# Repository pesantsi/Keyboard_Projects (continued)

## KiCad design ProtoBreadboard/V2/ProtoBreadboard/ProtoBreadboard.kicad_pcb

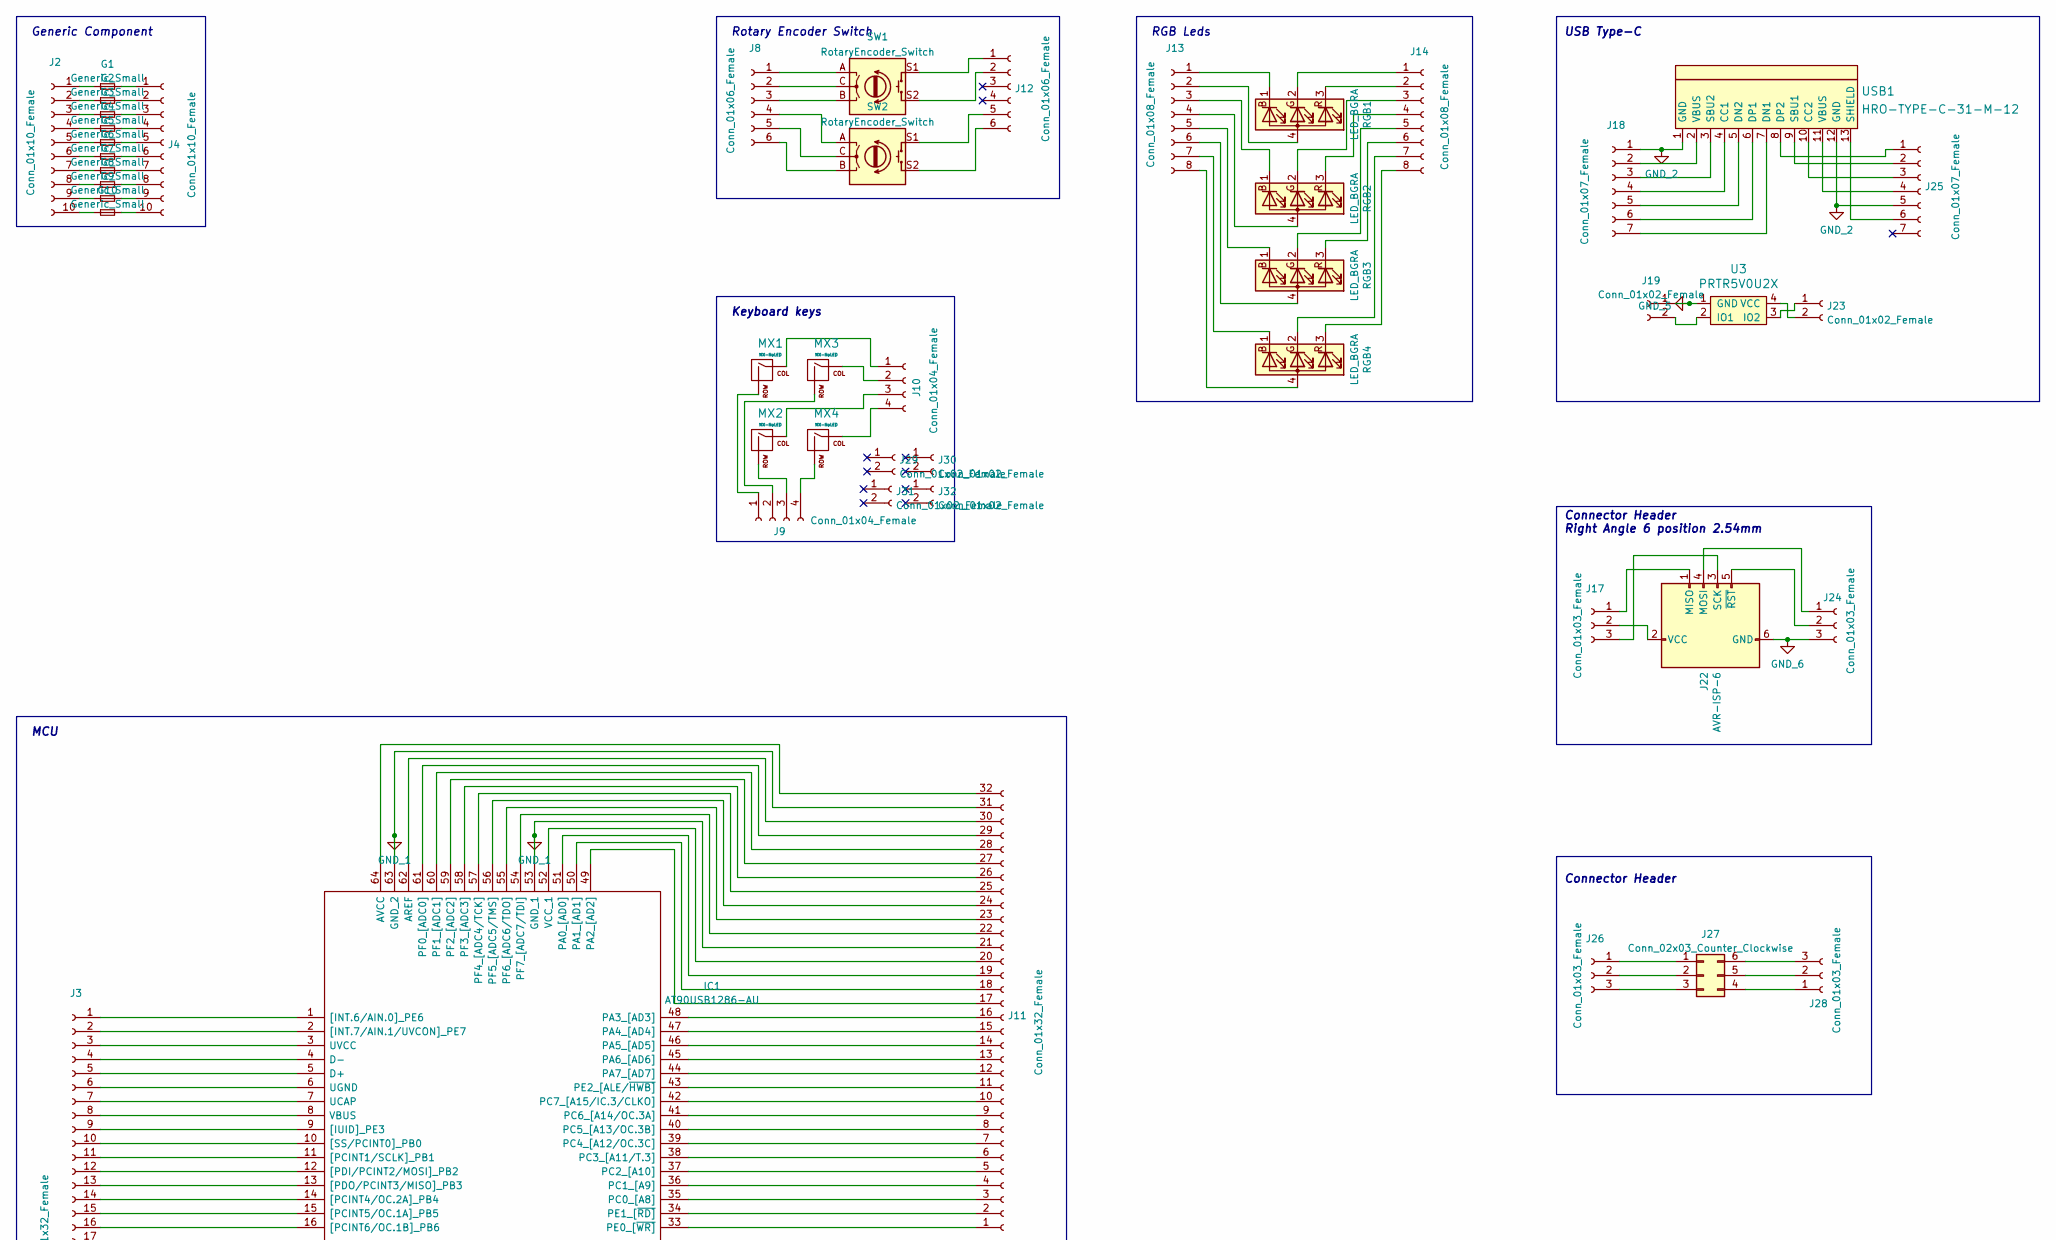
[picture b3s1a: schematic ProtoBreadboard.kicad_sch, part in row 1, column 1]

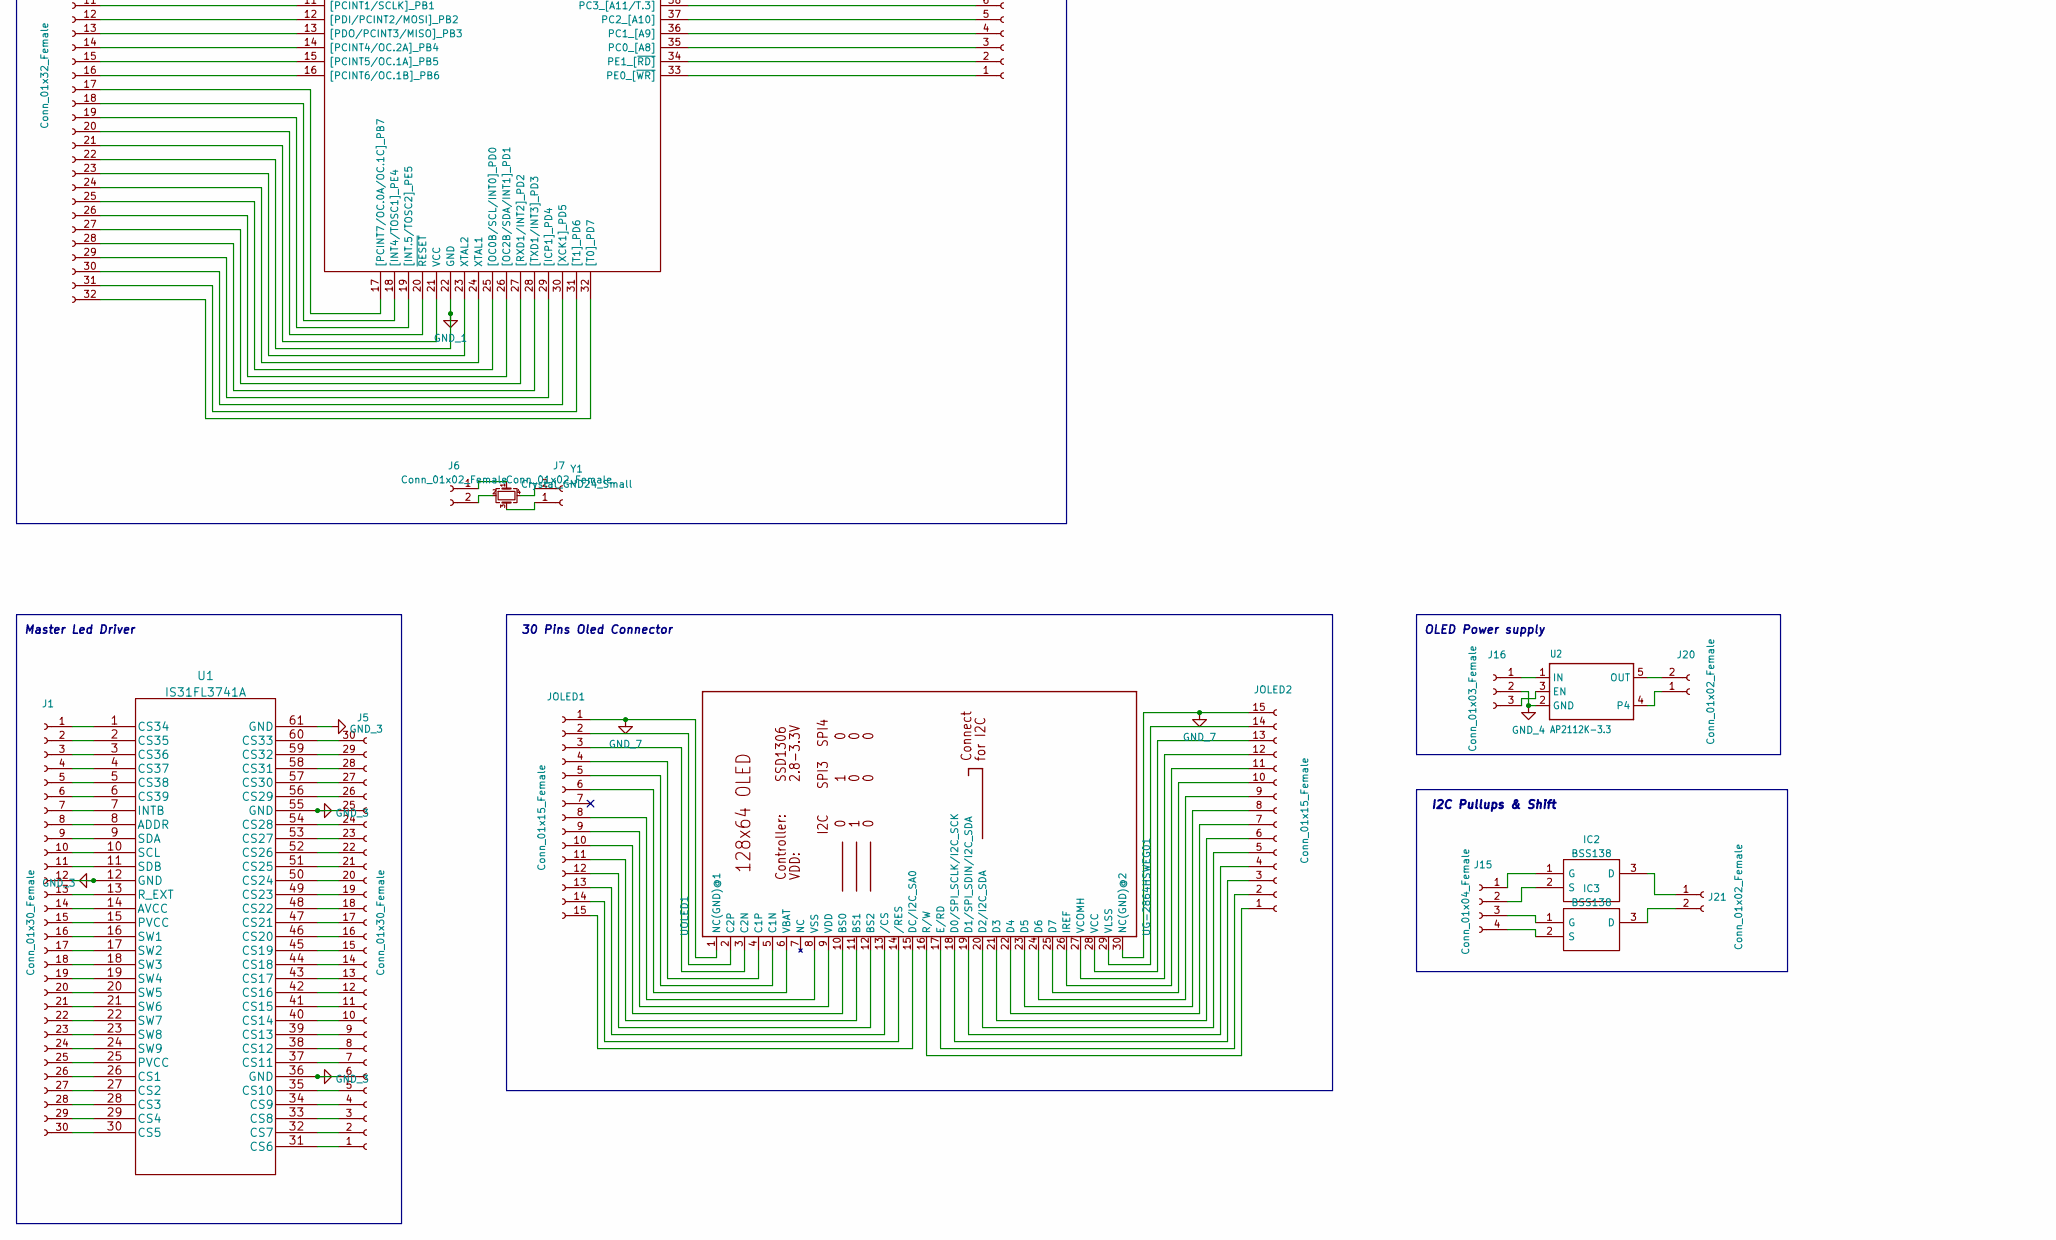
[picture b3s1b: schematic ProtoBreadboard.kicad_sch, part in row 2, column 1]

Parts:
G1, G2, G3, G4, G5, G6, G7, G8, G9, G10: Generic_Small; Generic
IC1: AT90USB1286-AU; Mouser Part Number 556-AT90USB1286-AU
IC2, IC3: BSS138; SOT95P240X120-3N; Manufacturer_Part_Number BSS138; Mouser Part Number 512-BSS138
J1, J5: Conn_01x30_Female; PinHeader_1x30_P2.54mm_Vertical
J2, J4: Conn_01x10_Female; PinHeader_1x10_P2.54mm_Vertical
J3, J11: Conn_01x32_Female; PinHeader_1x32_P2.54mm_Vertical
J6, J7, J19, J20, J21, J23, J29, J30, J31, J32: Conn_01x02_Female; PinHeader_1x02_P2.54mm_Vertical
J8, J12: Conn_01x06_Female; PinHeader_1x06_P2.54mm_Vertical
J9, J10, J15: Conn_01x04_Female; PinHeader_1x04_P2.54mm_Vertical
J13, J14: Conn_01x08_Female; PinHeader_1x08_P2.54mm_Vertical
J16, J17, J24, J26, J28: Conn_01x03_Female; PinHeader_1x03_P2.54mm_Vertical
J18, J25: Conn_01x07_Female; PinHeader_1x07_P2.54mm_Vertical
J22: AVR-ISP-6; PinHeader_2x03_P2.54mm_Vertical
J27: Conn_02x03_Counter_Clockwise; PinHeader_2x03_P2.54mm_Vertical
JOLED1, JOLED2: Conn_01x15_Female; PinHeader_1x15_P2.54mm_Vertical
MX1, MX2, MX3, MX4: MX-NoLED; MXOnly-1U-NoLED_3Pins
RGB1, RGB2, RGB3, RGB4: LED_BGRA; QBLP677R-RGB
SW1, SW2: RotaryEncoder_Switch; RotaryEncoder_Alps_EC12E-Switch_Vertical_H20mm
U1: IS31FL3741A; QFN40P700X700X80-61N-D
U2: AP2112K-3.3; SOT-23-5
U3: PRTR5V0U2X; SOT143B
UOLED1: UG-2864HSWEG01; 5051103091
USB1: HRO-TYPE-C-31-M-12
Y1: Crystal_GND24_Small; Crystal_SMD_3225-4Pin_3.2x2.5mm

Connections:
GND_1: IC1.22 (GND), IC1.53 (GND_1), IC1.63 (GND_2), J3.22, J11.21, J11.31
GND_2: J18.1, J25.5, USB1.1 (GND), USB1.12 (GND)
GND_3: J1.12, J5.6, J5.25, U1.12 (GND), U1.36 (GND), U1.55 (GND), U1.61 (GND)
GND_4: J16.2, U2.2 (GND)
GND_5: J19.1, U3.1 (GND)
GND_6: J22.6 (GND), J24.3
GND_7: JOLED1.1, JOLED2.15, UOLED1.1 (NC(GND)@1), UOLED1.30 (NC(GND)@2)
unnamed: G1.1, J2.1
unnamed: G1.2, J4.1
unnamed: G2.1, J2.2
unnamed: G2.2, J4.2
unnamed: G3.1, J2.3
unnamed: G3.2, J4.3
unnamed: G4.1, J2.4
unnamed: G4.2, J4.4
unnamed: G5.1, J2.5
unnamed: G5.2, J4.5
unnamed: G6.1, J2.6
unnamed: G6.2, J4.6
unnamed: G7.1, J2.7
unnamed: G7.2, J4.7
unnamed: G8.1, J2.8
unnamed: G8.2, J4.8
unnamed: G9.1, J2.9
unnamed: G9.2, J4.9
unnamed: G10.1, J2.10
unnamed: G10.2, J4.10
unnamed: IC1.1 ([INT.6/AIN.0]_PE6), J3.1
unnamed: IC1.2 ([INT.7/AIN.1/UVCON]_PE7), J3.2
unnamed: IC1.3 (UVCC), J3.3
unnamed: IC1.4 (D-), J3.4
unnamed: IC1.5 (D+), J3.5
unnamed: IC1.6 (UGND), J3.6
unnamed: IC1.7 (UCAP), J3.7
unnamed: IC1.8 (VBUS), J3.8
unnamed: IC1.9 ([IUID]_PE3), J3.9
unnamed: IC1.10 ([SS/PCINT0]_PB0), J3.10
unnamed: IC1.11 ([PCINT1/SCLK]_PB1), J3.11
unnamed: IC1.12 ([PDI/PCINT2/MOSI]_PB2), J3.12
unnamed: IC1.13 ([PDO/PCINT3/MISO]_PB3), J3.13
unnamed: IC1.14 ([PCINT4/OC.2A]_PB4), J3.14
unnamed: IC1.15 ([PCINT5/OC.1A]_PB5), J3.15
unnamed: IC1.16 ([PCINT6/OC.1B]_PB6), J3.16
unnamed: IC1.17 ([PCINT7/OC.0A/OC.1C]_PB7), J3.17
unnamed: IC1.18 ([INT4/TOSC1]_PE4), J3.18
unnamed: IC1.19 ([INT.5/TOSC2]_PE5), J3.19
unnamed: IC1.20 (~RESET), J3.20
unnamed: IC1.21 (VCC), J3.21
unnamed: IC1.23 (XTAL2), J3.23
unnamed: IC1.24 (XTAL1), J3.24
unnamed: IC1.25 ([OC0B/SCL/INT0]_PD0), J3.25
unnamed: IC1.26 ([OC2B/SDA/INT1]_PD1), J3.26
unnamed: IC1.27 ([RXD1/INT2]_PD2), J3.27
unnamed: IC1.28 ([TXD1/INT3]_PD3), J3.28
unnamed: IC1.29 ([ICP1]_PD4), J3.29
unnamed: IC1.30 ([XCK1]_PD5), J3.30
unnamed: IC1.31 ([T1]_PD6), J3.31
unnamed: IC1.32 ([T0]_PD7), J3.32
unnamed: IC1.33 (PE0_[~WR]), J11.1
unnamed: IC1.34 (PE1_[~RD]), J11.2
unnamed: IC1.35 (PC0_[A8]), J11.3
unnamed: IC1.36 (PC1_[A9]), J11.4
unnamed: IC1.37 (PC2_[A10]), J11.5
unnamed: IC1.38 (PC3_[A11/T.3]), J11.6
unnamed: IC1.39 (PC4_[A12/OC.3C]), J11.7
unnamed: IC1.40 (PC5_[A13/OC.3B]), J11.8
unnamed: IC1.41 (PC6_[A14/OC.3A]), J11.9
unnamed: IC1.42 (PC7_[A15/IC.3/CLKO]), J11.10
unnamed: IC1.43 (PE2_[ALE/~HWB]), J11.11
unnamed: IC1.44 (PA7_[AD7]), J11.12
unnamed: IC1.45 (PA6_[AD6]), J11.13
unnamed: IC1.46 (PA5_[AD5]), J11.14
unnamed: IC1.47 (PA4_[AD4]), J11.15
unnamed: IC1.48 (PA3_[AD3]), J11.16
unnamed: IC1.49 (PA2_[AD2]), J11.17
unnamed: IC1.50 (PA1_[AD1]), J11.18
unnamed: IC1.51 (PA0_[AD0]), J11.19
unnamed: IC1.52 (VCC_1), J11.20
unnamed: IC1.54 (PF7_[ADC7/TDI]), J11.22
unnamed: IC1.55 (PF6_[ADC6/TDO]), J11.23
unnamed: IC1.56 (PF5_[ADC5/TMS]), J11.24
unnamed: IC1.57 (PF4_[ADC4/TCK]), J11.25
unnamed: IC1.58 (PF3_[ADC3]), J11.26
unnamed: IC1.59 (PF2_[ADC2]), J11.27
unnamed: IC1.60 (PF1_[ADC1]), J11.28
unnamed: IC1.61 (PF0_[ADC0]), J11.29
unnamed: IC1.62 (AREF), J11.30
unnamed: IC1.64 (AVCC), J11.32
unnamed: IC2.1 (G), J15.1
unnamed: IC2.2 (S), J15.2
unnamed: IC2.3 (D), J21.1
unnamed: IC3.1 (G), J15.3
unnamed: IC3.2 (S), J15.4
unnamed: IC3.3 (D), J21.2
unnamed: J1.1, U1.1 (CS34)
unnamed: J1.2, U1.2 (CS35)
unnamed: J1.3, U1.3 (CS36)
unnamed: J1.4, U1.4 (CS37)
unnamed: J1.5, U1.5 (CS38)
unnamed: J1.6, U1.6 (CS39)
unnamed: J1.7, U1.7 (INTB)
unnamed: J1.8, U1.8 (ADDR)
unnamed: J1.9, U1.9 (SDA)
unnamed: J1.10, U1.10 (SCL)
unnamed: J1.11, U1.11 (SDB)
unnamed: J1.13, U1.13 (R_EXT)
unnamed: J1.14, U1.14 (AVCC)
unnamed: J1.15, U1.15 (PVCC)
unnamed: J1.16, U1.16 (SW1)
unnamed: J1.17, U1.17 (SW2)
unnamed: J1.18, U1.18 (SW3)
unnamed: J1.19, U1.19 (SW4)
unnamed: J1.20, U1.20 (SW5)
unnamed: J1.21, U1.21 (SW6)
unnamed: J1.22, U1.22 (SW7)
unnamed: J1.23, U1.23 (SW8)
unnamed: J1.24, U1.24 (SW9)
unnamed: J1.25, U1.25 (PVCC)
unnamed: J1.26, U1.26 (CS1)
unnamed: J1.27, U1.27 (CS2)
unnamed: J1.28, U1.28 (CS3)
unnamed: J1.29, U1.29 (CS4)
unnamed: J1.30, U1.30 (CS5)
unnamed: J5.1, U1.31 (CS6)
unnamed: J5.2, U1.32 (CS7)
unnamed: J5.3, U1.33 (CS8)
unnamed: J5.4, U1.34 (CS9)
unnamed: J5.5, U1.35 (CS10)
unnamed: J5.7, U1.37 (CS11)
unnamed: J5.8, U1.38 (CS12)
unnamed: J5.9, U1.39 (CS13)
unnamed: J5.10, U1.40 (CS14)
unnamed: J5.11, U1.41 (CS15)
unnamed: J5.12, U1.42 (CS16)
unnamed: J5.13, U1.43 (CS17)
unnamed: J5.14, U1.44 (CS18)
unnamed: J5.15, U1.45 (CS19)
unnamed: J5.16, U1.46 (CS20)
unnamed: J5.17, U1.47 (CS21)
unnamed: J5.18, U1.48 (CS22)
unnamed: J5.19, U1.49 (CS23)
unnamed: J5.20, U1.50 (CS24)
unnamed: J5.21, U1.51 (CS25)
unnamed: J5.22, U1.52 (CS26)
unnamed: J5.23, U1.53 (CS27)
unnamed: J5.24, U1.54 (CS28)
unnamed: J5.26, U1.56 (CS29)
unnamed: J5.27, U1.57 (CS30)
unnamed: J5.28, U1.58 (CS31)
unnamed: J5.29, U1.59 (CS32)
unnamed: J5.30, U1.60 (CS33)
unnamed: J6.1, Y1.1
unnamed: J6.2, Y1.2
unnamed: J7.1, Y1.3
unnamed: J7.2, Y1.4
unnamed: J8.1, SW1.A
unnamed: J8.2, SW1.C
unnamed: J8.3, SW1.B
unnamed: J8.4, SW2.A
unnamed: J8.5, SW2.C
unnamed: J8.6, SW2.B
unnamed: J9.1, MX1.2 (ROW)
unnamed: J9.2, MX3.2 (ROW)
unnamed: J9.3, MX2.2 (ROW)
unnamed: J9.4, MX4.2 (ROW)
unnamed: J10.1, MX1.1 (COL)
unnamed: J10.2, MX3.1 (COL)
unnamed: J10.3, MX2.1 (COL)
unnamed: J10.4, MX4.1 (COL)
unnamed: J13.1, RGB1.1 (BK)
unnamed: J13.2, RGB1.4 (A)
unnamed: J13.3, RGB2.1 (BK)
unnamed: J13.4, RGB2.4 (A)
unnamed: J13.5, RGB3.1 (BK)
unnamed: J13.6, RGB3.4 (A)
unnamed: J13.7, RGB4.1 (BK)
unnamed: J13.8, RGB4.4 (A)
unnamed: J14.1, RGB1.2 (GK)
unnamed: J14.2, RGB1.3 (RK)
unnamed: J14.3, RGB2.2 (GK)
unnamed: J14.4, RGB2.3 (RK)
unnamed: J14.5, RGB3.2 (GK)
unnamed: J14.6, RGB3.3 (RK)
unnamed: J14.7, RGB4.2 (GK)
unnamed: J14.8, RGB4.3 (RK)
unnamed: J16.1, U2.1 (IN)
unnamed: J16.3, U2.3 (EN)
unnamed: J17.1, J22.1 (MISO)
unnamed: J17.2, J22.2 (VCC)
unnamed: J17.3, J22.3 (SCK)
unnamed: J18.2, USB1.2 (VBUS)
unnamed: J18.3, USB1.3 (SBU2)
unnamed: J18.4, USB1.4 (CC1)
unnamed: J18.5, USB1.5 (DN2)
unnamed: J18.6, USB1.6 (DP1)
unnamed: J18.7, USB1.7 (DN1)
unnamed: J19.2, U3.2 (IO1)
unnamed: J20.1, U2.4
unnamed: J20.2, U2.5 (OUT)
unnamed: J22.4 (MOSI), J24.1
unnamed: J22.5 (~RST), J24.2
unnamed: J23.1, U3.3 (IO2)
unnamed: J23.2, U3.4 (VCC)
unnamed: J25.1, USB1.8 (DP2)
unnamed: J25.2, USB1.9 (SBU1)
unnamed: J25.3, USB1.10 (CC2)
unnamed: J25.4, USB1.11 (VBUS)
unnamed: J25.6, USB1.13 (SHIELD)
unnamed: J26.1, J27.1
unnamed: J26.2, J27.2
unnamed: J26.3, J27.3
unnamed: J27.4, J28.1
unnamed: J27.5, J28.2
unnamed: J27.6, J28.3
unnamed: JOLED1.2, UOLED1.2 (C2P)
unnamed: JOLED1.3, UOLED1.3 (C2N)
unnamed: JOLED1.4, UOLED1.4 (C1P)
unnamed: JOLED1.5, UOLED1.5 (C1N)
unnamed: JOLED1.6, UOLED1.6 (VBAT)
unnamed: JOLED1.8, UOLED1.8 (VSS)
unnamed: JOLED1.9, UOLED1.9 (VDD)
unnamed: JOLED1.10, UOLED1.10 (BS0)
unnamed: JOLED1.11, UOLED1.11 (BS1)
unnamed: JOLED1.12, UOLED1.12 (BS2)
unnamed: JOLED1.13, UOLED1.13 (/CS)
unnamed: JOLED1.14, UOLED1.14 (/RES)
unnamed: JOLED1.15, UOLED1.15 (DC/I2C_SA0)
unnamed: JOLED2.1, UOLED1.16 (R/W)
unnamed: JOLED2.2, UOLED1.17 (E/RD)
unnamed: JOLED2.3, UOLED1.18 (D0/SPI_SCLK/I2C_SCK)
unnamed: JOLED2.4, UOLED1.19 (D1/SPI_SDIN/I2C_SDA)
unnamed: JOLED2.5, UOLED1.20 (D2/I2C_SDA)
unnamed: JOLED2.6, UOLED1.21 (D3)
unnamed: JOLED2.7, UOLED1.22 (D4)
unnamed: JOLED2.8, UOLED1.23 (D5)
unnamed: JOLED2.9, UOLED1.24 (D6)
unnamed: JOLED2.10, UOLED1.25 (D7)
unnamed: JOLED2.11, UOLED1.26 (IREF)
unnamed: JOLED2.12, UOLED1.27 (VCOMH)
unnamed: JOLED2.13, UOLED1.28 (VCC)
unnamed: JOLED2.14, UOLED1.29 (VLSS)
unnamed: J12.1, SW1.S1
unnamed: J12.2, SW1.S2
unnamed: J12.5, SW2.S1
unnamed: J12.6, SW2.S2

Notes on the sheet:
Keyboard keys
30 Pins Oled Connector
Master Led Driver
Connector Header Right Angle 6 position 2.54mm
RGB Leds
Generic Component
OLED Power supply
MCU
USB Type-C
I2C Pullups & Shift
Rotary Encoder Switch
Connector Header

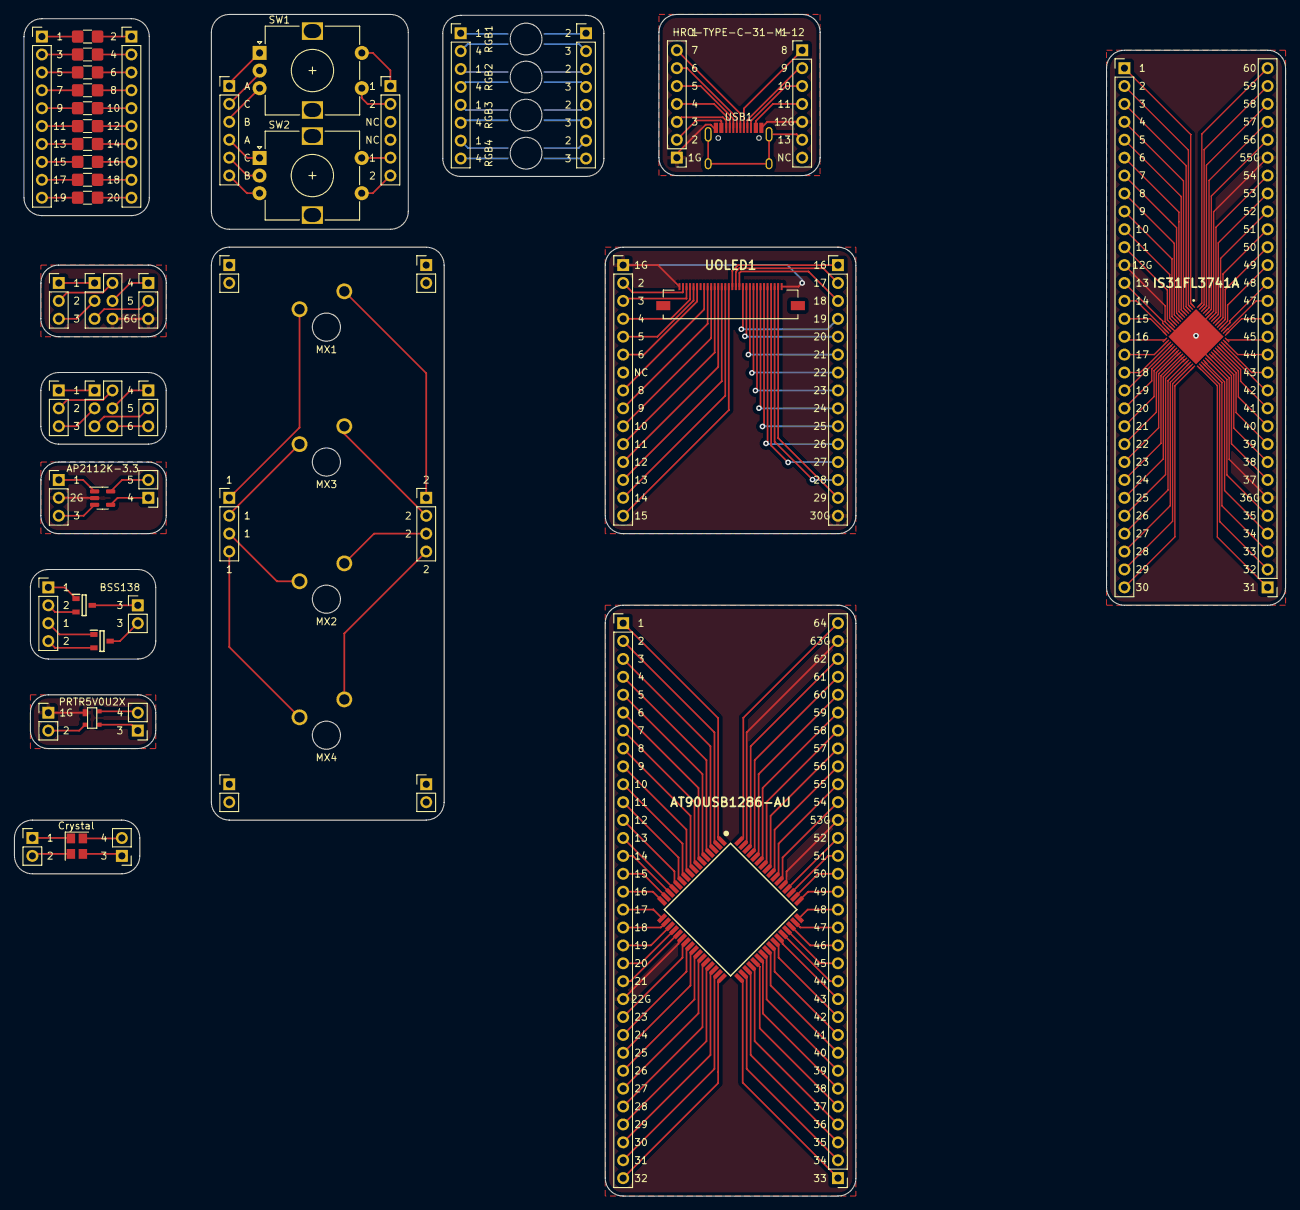
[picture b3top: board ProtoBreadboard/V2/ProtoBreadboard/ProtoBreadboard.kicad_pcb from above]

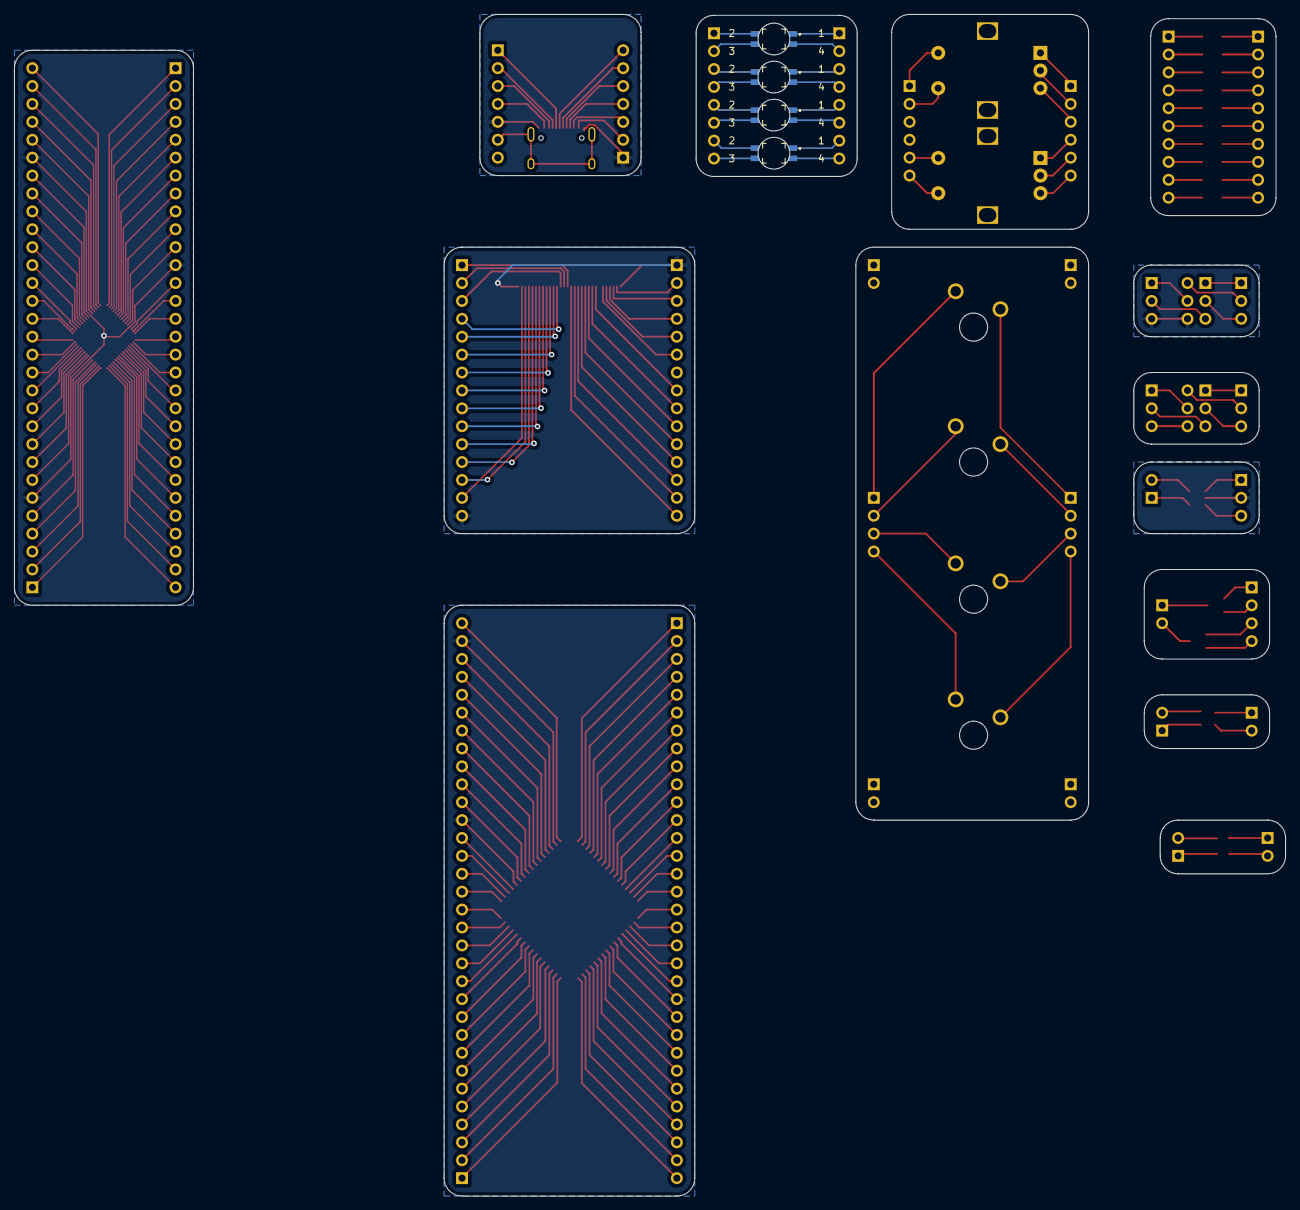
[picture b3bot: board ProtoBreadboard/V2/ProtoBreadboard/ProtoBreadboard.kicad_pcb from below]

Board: 2 copper layers, 180.3 x 167.6 mm, 63 parts (4 on the bottom side), 245 nets.

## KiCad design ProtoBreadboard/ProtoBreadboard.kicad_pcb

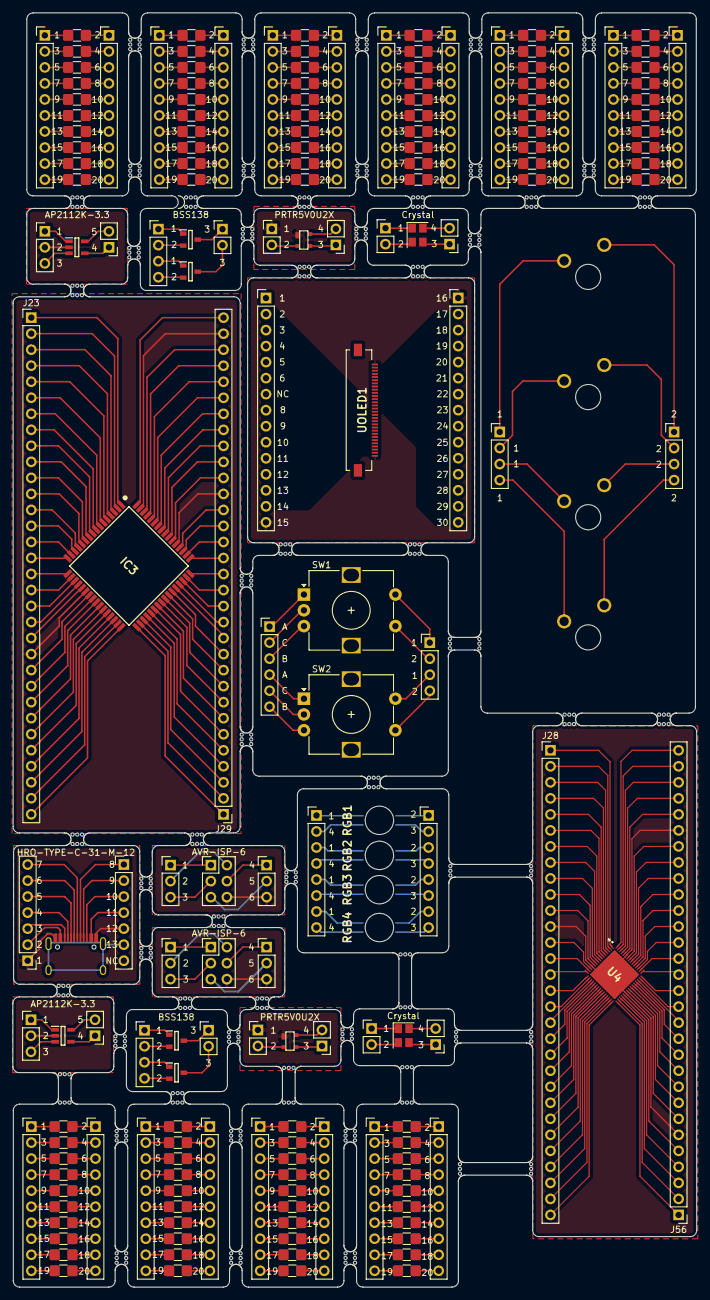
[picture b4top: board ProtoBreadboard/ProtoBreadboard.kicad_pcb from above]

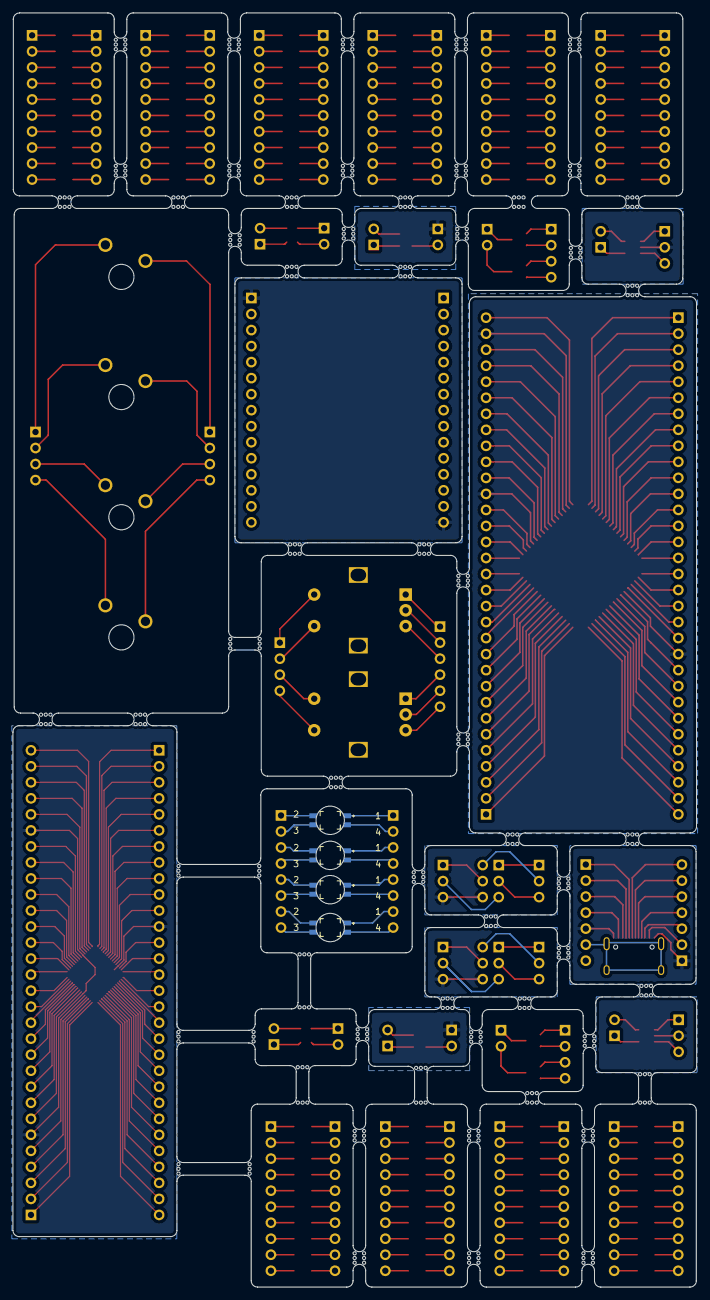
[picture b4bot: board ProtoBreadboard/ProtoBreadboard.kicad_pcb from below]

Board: 2 copper layers, 108.4 x 202.0 mm, 245 parts (4 on the bottom side), 144 nets.

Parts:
G1, G2, G3, G4, G5, G6, G7, G8, G9, G10, G11, G12, G13, G14, G15, G16, G17, G18, G19, G20, G21, G22, G23, G24, G25, G26, G27, G28, G29, G30, G31, G32, G33, G34, G35, G36, G37, G38, G39, G40, G41, G42, G43, G44, G45, G46, G47, G48, G49, G50, G51, G52, G53, G54, G55, G56, G57, G58, G59, G60, G61, G62, G63, G64, G65, G66, G67, G68, G69, G70, G71, G72, G73, G74, G75, G76, G77, G78, G79, G80, G81, G82, G83, G84, G85, G86, G87, G88, G89, G90, G91, G92, G93, G94, G95, G96, G97, G98, G99, G100: Generic_Small; Generic
IC1, IC2, IC4, IC5: BSS138; SOT95P240X120-3N
IC3: AT90USB1286-AU
J1, J2, J3, J4, J5, J6, J7, J8, J9, J10, J11, J12, J48, J49, J50, J51, J52, J53, J54, J55: Conn_01x10_Female; PinHeader_1x10_P2.54mm_Vertical
J13, J14, J17, J18, J19, J20, J41, J42, J44, J45, J46, J47: Conn_01x02_Female; PinHeader_1x02_P2.54mm_Vertical
J15, J24, J25, J27, J43: Conn_01x04_Female; PinHeader_1x04_P2.54mm_Vertical
J16, J33, J35, J36, J38, J40: Conn_01x03_Female; PinHeader_1x03_P2.54mm_Vertical
J23, J29: Conn_01x32_Female; PinHeader_1x32_P2.54mm_Vertical
J26: Conn_01x06_Female; PinHeader_1x06_P2.54mm_Vertical
J28, J56: Conn_01x30_Female; PinHeader_1x30_P2.54mm_Vertical
J30, J31: Conn_01x08_Female; PinHeader_1x08_P2.54mm_Vertical
J32, J39: Conn_01x07_Female; PinHeader_1x07_P2.54mm_Vertical
J34, J37: AVR-ISP-6; PinHeader_2x03_P2.54mm_Vertical
JOLED1, JOLED2: Conn_01x15_Female; PinHeader_1x15_P2.54mm_Vertical
MX1, MX2, MX3, MX4: MX-NoLED; MXOnly-1U-NoLED_3Pins
RGB1, RGB2, RGB3, RGB4: LED_BGRA; QBLP677R-RGB
SW1, SW2: RotaryEncoder_Switch; RotaryEncoder_Alps_EC12E-Switch_Vertical_H20mm
U1, U6: PRTR5V0U2X; SOT143B
U2, U5: AP2112K-3.3; SOT95P282X130-5N
U4: QFN40P700X700X80-61N-D
UOLED1: UG-2864HSWEG01; 5051103091
USB1: HRO-TYPE-C-31-M-12
Y1, Y2: Crystal; Crystal_SMD_3225-4Pin_3.2x2.5mm
mouse-bite-1, mouse-bite-2, mouse-bite-3, mouse-bite-4, mouse-bite-5, mouse-bite-6, mouse-bite-7, mouse-bite-8, mouse-bite-9, mouse-bite-10, mouse-bite-11, mouse-bite-12, mouse-bite-13, mouse-bite-14, mouse-bite-15, mouse-bite-16, mouse-bite-17, mouse-bite-18, mouse-bite-19, mouse-bite-20, mouse-bite-21, mouse-bite-22, mouse-bite-23, mouse-bite-24, mouse-bite-25, mouse-bite-26, mouse-bite-29, mouse-bite-30, mouse-bite-31, mouse-bite-32, mouse-bite-33, mouse-bite-34, mouse-bite-37, mouse-bite-38, mouse-bite-39, mouse-bite-40, mouse-bite-42, mouse-bite-44, mouse-bite-45, mouse-bite-46, mouse-bite-47, mouse-bite-50, mouse-bite-55, mouse-bite-58, mouse-bite-59, mouse-bite-60, mouse-bite-63, mouse-bite-64, mouse-bite-65: VAL**; mouse-bite-2mm-slot
mouse-bite-27, mouse-bite-28, mouse-bite-35, mouse-bite-36, mouse-bite-41, mouse-bite-43, mouse-bite-48, mouse-bite-49, mouse-bite-51, mouse-bite-52, mouse-bite-53, mouse-bite-54, mouse-bite-56, mouse-bite-57, mouse-bite-61, mouse-bite-62: VAL**; mouse-bite-2mm-slot-1-side

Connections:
GND_1: IC3.22 (GND), IC3.53 (GND_1), IC3.63 (GND_2), J29.21, J29.31
GND_2: J15.1, J32.5, J39.1, USB1.1 (GND), USB1.12 (GND)
GND_3: J4.6, J28.12, J56.6, J56.25
GND_4: J23.2, J40.2, U4.2 (GND), U5.2 (GND)
GND_5: J19.1, J42.1, U2.1 (GND), U6.1 (GND)
GND_6: J34.6 (GND), J35.3, J37.6 (GND), J38.3
GND_7: JOLED1.15, JOLED2.1, UOLED1.1 (NC(GND)@1), UOLED1.30 (NC(GND)@2)
unnamed: G1.1, G61.1, G62.1, G63.1, G64.1, J1.1, J48.1, J50.1, J52.1, J54.1
unnamed: G1.2, G61.2, G62.2, G63.2, G64.2, J2.1, J49.1, J51.1, J53.1, J55.1
unnamed: G2.1, G11.1, G12.1, G65.1, G66.1, G67.1, G68.1, J1.2, J48.2, J50.2, J52.2, J54.2
unnamed: G2.2, G11.2, G12.2, G65.2, G66.2, G67.2, G68.2, J2.2, J49.2, J51.2, J53.2, J55.2
unnamed: G3.1, G13.1, G14.1, G15.1, G16.1, G17.1, G18.1, G69.1, G70.1, G71.1, G72.1, J1.3, J48.3, J50.3, J52.3, J54.3
unnamed: G3.2, G13.2, G14.2, G15.2, G16.2, G17.2, G18.2, G69.2, G70.2, G71.2, G72.2, J2.3, J49.3, J51.3, J53.3, J55.3
unnamed: G4.1, G19.1, G20.1, G21.1, G22.1, G23.1, G24.1, G73.1, G74.1, G75.1, G76.1, J1.4, J48.4, J50.4, J52.4, J54.4
unnamed: G4.2, G19.2, G20.2, G21.2, G22.2, G23.2, G24.2, G73.2, G74.2, G75.2, G76.2, J2.4, J49.4, J51.4, J53.4, J55.4
unnamed: G5.1, G25.1, G26.1, G27.1, G28.1, G29.1, G30.1, G77.1, G78.1, G79.1, G80.1, J1.5, J48.5, J50.5, J52.5, J54.5
unnamed: G5.2, G25.2, G26.2, G27.2, G28.2, G29.2, G30.2, G77.2, G78.2, G79.2, G80.2, J2.5, J49.5, J51.5, J53.5, J55.5
unnamed: G6.1, G31.1, G32.1, G33.1, G34.1, G35.1, G36.1, G81.1, G82.1, G83.1, G84.1, J1.6, J48.6, J50.6, J52.6, J54.6
unnamed: G6.2, G31.2, G32.2, G33.2, G34.2, G35.2, G36.2, G81.2, G82.2, G83.2, G84.2, J2.6, J49.6, J51.6, J53.6, J55.6
unnamed: G7.1, G37.1, G38.1, G39.1, G40.1, G41.1, G42.1, G85.1, G86.1, G87.1, G88.1, J1.7, J48.7, J50.7, J52.7, J54.7
unnamed: G7.2, G37.2, G38.2, G39.2, G40.2, G41.2, G42.2, G85.2, G86.2, G87.2, G88.2, J2.7, J49.7, J51.7, J53.7, J55.7
unnamed: G8.1, G43.1, G44.1, G45.1, G46.1, G47.1, G48.1, G89.1, G90.1, G91.1, G92.1, J1.8, J48.8, J50.8, J52.8, J54.8
unnamed: G8.2, G43.2, G44.2, G45.2, G46.2, G47.2, G48.2, G89.2, G90.2, G91.2, G92.2, J2.8, J49.8, J51.8, J53.8, J55.8
unnamed: G9.1, G49.1, G50.1, G51.1, G52.1, G53.1, G54.1, G93.1, G94.1, G95.1, G96.1, J1.9, J48.9, J50.9, J52.9, J54.9
unnamed: G9.2, G49.2, G50.2, G51.2, G52.2, G53.2, G54.2, G93.2, G94.2, G95.2, G96.2, J2.9, J49.9, J51.9, J53.9, J55.9
unnamed: G10.1, G55.1, G56.1, G57.1, G58.1, G59.1, G60.1, G97.1, G98.1, G99.1, G100.1, J1.10, J48.10, J50.10, J52.10, J54.10
unnamed: G10.2, G55.2, G56.2, G57.2, G58.2, G59.2, G60.2, G97.2, G98.2, G99.2, G100.2, J2.10, J49.10, J51.10, J53.10, J55.10
unnamed: IC1.1 (G), IC4.1 (G), J26.1, J43.1
unnamed: IC1.2 (S), IC4.2 (S), J26.2, J43.2
unnamed: IC1.3 (D), IC4.3 (D), J17.1 (MISO), J25.1, J45.1
unnamed: IC2.1 (G), IC5.1 (G), J26.3, J43.3
unnamed: IC2.2 (S), IC5.2 (S), J26.4, J43.4
unnamed: IC2.3 (D), IC5.3 (D), J17.2 (VCC), J25.2, J45.2
unnamed: IC3.1 ([INT.6/AIN.0]_PE6), J13.1
unnamed: IC3.2 ([INT.7/AIN.1/UVCON]_PE7), J13.2
unnamed: IC3.33 (PE0_[~WR]), J14.1
unnamed: IC3.34 (PE1_[~RD]), J14.2
unnamed: J3.1, J28.1, U1.1 (CS34)
unnamed: J3.2, J28.2, U1.2 (CS35)
unnamed: J3.3, J28.3, U1.3 (CS36)
unnamed: J3.4, J28.4, U1.4 (CS37)
unnamed: J3.5, J28.5
unnamed: J3.6, J28.6
unnamed: J3.7, J28.7
unnamed: J3.8, J28.8
unnamed: J3.9, J28.9
unnamed: J3.10, J28.10
unnamed: J4.1, J56.1
unnamed: J4.2, J56.2
unnamed: J4.3, J56.3
unnamed: J4.4, J56.4
unnamed: J4.5, J56.5
unnamed: J4.7, J56.7
unnamed: J4.8, J56.8
unnamed: J4.9, J56.9
unnamed: J4.10, J56.10
unnamed: J5.1, J41.1, Y1.1, Y2.1
unnamed: J5.2, J41.2, Y1.2, Y2.2
unnamed: J6.1, J46.1, Y1.3, Y2.3
unnamed: J6.2, J46.2, Y1.4, Y2.4
unnamed: J7.1, MX1.1 (COL)
unnamed: J7.2, MX2.1 (COL)
unnamed: J7.3, MX3.1 (COL)
unnamed: J7.4, MX4.1 (COL)
unnamed: J9.1, J30.1, RGB1.1 (BK)
unnamed: J9.2, J30.2, RGB1.4 (A)
unnamed: J9.3, J30.3, RGB2.1 (BK)
unnamed: J9.4, J30.4, RGB2.4 (A)
unnamed: J9.5, J30.5, RGB3.1 (BK)
unnamed: J9.6, J30.6, RGB3.4 (A)
unnamed: J9.7, J30.7, RGB4.1 (BK)
unnamed: J9.8, J30.8, RGB4.4 (A)
unnamed: J10.1, J31.1, RGB1.2 (GK)
unnamed: J10.2, J31.2, RGB1.3 (RK)
unnamed: J10.3, J31.3, RGB2.2 (GK)
unnamed: J10.4, J31.4, RGB2.3 (RK)
unnamed: J10.5, J31.5, RGB3.2 (GK)
unnamed: J10.6, J31.6, RGB3.3 (RK)
unnamed: J10.7, J31.7, RGB4.2 (GK)
unnamed: J10.8, J31.8, RGB4.3 (RK)
unnamed: J11.1, SW1.A
unnamed: J11.2, SW1.C
unnamed: J11.3, SW1.B
unnamed: J11.4, SW2.A
unnamed: J11.5, SW2.C
unnamed: J11.6, SW2.B
unnamed: J12.1, SW1.S1
unnamed: J12.2, SW1.S2
unnamed: J12.3, SW2.S1
unnamed: J12.4, SW2.S2
unnamed: J15.2, J39.2, USB1.2 (VBUS)
unnamed: J15.3, J39.3, USB1.3 (SBU2)
unnamed: J15.4, J39.4, USB1.4 (CC1)
unnamed: J39.5, USB1.5 (DN2)
unnamed: J39.6, USB1.6 (DP1)
unnamed: J39.7, USB1.7 (DN1)
unnamed: J16.1, J32.1, USB1.8 (DP2)
unnamed: J16.2, J32.2, USB1.9 (SBU1)
unnamed: J16.3, J32.3, USB1.10 (CC2)
unnamed: J32.4, USB1.11 (VBUS)
unnamed: J32.6, USB1.13 (SHIELD)
unnamed: J8.1, J33.1, J34.1 (MISO), J36.1, J37.1 (MISO)
unnamed: J8.2, J33.2, J34.2 (VCC), J36.2, J37.2 (VCC)
unnamed: J8.3, J33.3, J34.3 (SCK), J36.3, J37.3 (SCK)
unnamed: J18.1, J34.4 (MOSI), J35.1, J37.4 (MOSI), J38.1
unnamed: J18.2, J34.5 (~RST), J35.2, J37.5 (~RST), J38.2
unnamed: J19.2, J42.2, U2.2 (IO1), U6.2 (IO1)
unnamed: J20.1, J47.1, U2.3 (IO2), U6.3 (IO2)
unnamed: J20.2, J47.2, U2.4 (VCC), U6.4 (VCC)
unnamed: JOLED1.1, UOLED1.16 (R/W)
unnamed: JOLED1.2, UOLED1.17 (E/RD)
unnamed: JOLED1.3, UOLED1.18 (D0/SPI_SCLK/I2C_SCK)
unnamed: JOLED1.4, UOLED1.19 (D1/SPI_SDIN/I2C_SDA)
unnamed: JOLED1.5, UOLED1.20 (D2/I2C_SDA)
unnamed: JOLED1.6, UOLED1.21 (D3)
unnamed: JOLED1.7, UOLED1.22 (D4)
unnamed: JOLED1.8, UOLED1.23 (D5)
unnamed: JOLED1.9, UOLED1.24 (D6)
unnamed: JOLED1.10, UOLED1.25 (D7)
unnamed: JOLED1.11, UOLED1.26 (IREF)
unnamed: JOLED1.12, UOLED1.27 (VCOMH)
unnamed: JOLED1.13, UOLED1.28 (VCC)
unnamed: JOLED1.14, UOLED1.29 (VLSS)
unnamed: JOLED2.2, UOLED1.2 (C2P)
unnamed: JOLED2.3, UOLED1.3 (C2N)
unnamed: JOLED2.4, UOLED1.4 (C1P)
unnamed: JOLED2.5, UOLED1.5 (C1N)
unnamed: JOLED2.6, UOLED1.6 (VBAT)
unnamed: JOLED2.8, UOLED1.8 (VSS)
unnamed: JOLED2.9, UOLED1.9 (VDD)
unnamed: JOLED2.10, UOLED1.10 (BS0)
unnamed: JOLED2.11, UOLED1.11 (BS1)
unnamed: JOLED2.12, UOLED1.12 (BS2)
unnamed: JOLED2.13, UOLED1.13 (/CS)
unnamed: JOLED2.14, UOLED1.14 (/RES)
unnamed: JOLED2.15, UOLED1.15 (DC/I2C_SA0)
unnamed: J23.1, J40.1, U4.1 (IN), U5.1 (IN)
unnamed: J23.3, J40.3, U4.3 (EN), U5.3 (EN)
unnamed: J24.1, J44.1, U4.4, U5.4
unnamed: J24.2, J44.2, U4.5 (OUT), U5.5 (OUT)
unnamed: J27.1, MX1.2 (ROW)
unnamed: J27.2, MX2.2 (ROW)
unnamed: J27.3, MX3.2 (ROW)
unnamed: J27.4, MX4.2 (ROW)

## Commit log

2022-02-04 Adding submodules
2022-03-06 Updates on the schematics
2022-03-06 Added Docs
2022-03-07 Breadboad
2022-03-09 Breadboard Mouse Bits
2022-03-11 Almost Finished Panelizing
2022-03-13 Mouse Bits Finished
2022-03-14 Updated but something wrong
2022-03-14 Added V1 folder
2022-03-15 Finished V2 of breadboard and initial commit on panel project
2022-03-16 Completed V2 Breadboard
2022-03-16 First draft, egde cut remaining
2022-03-17 Fixing Edge Cut
2022-03-17 Completed Mouse bits
2022-03-17 Added one sided mouse bits
2022-03-20 Panel Gerber and Internet Shortcuts for proto
2022-03-21 Small alignment error for the crystal in the panel
2022-03-21 Fixing small crystal 2.54mm layout problem
2022-03-22 Spliy Panel into 3 design
2022-03-22 Added Gerber Files for all 3 new designs
2022-03-22 Remove unused submodule
2022-03-22 Main Panel Gerber for Stencil
2022-04-10 added oled adafruit link, removed useless csv
2022-04-15 Adding zip file from contractor
2022-04-15 Adding Sumkin
2022-04-21 Start working on pcb
2022-10-22 Master led driver connected properly
